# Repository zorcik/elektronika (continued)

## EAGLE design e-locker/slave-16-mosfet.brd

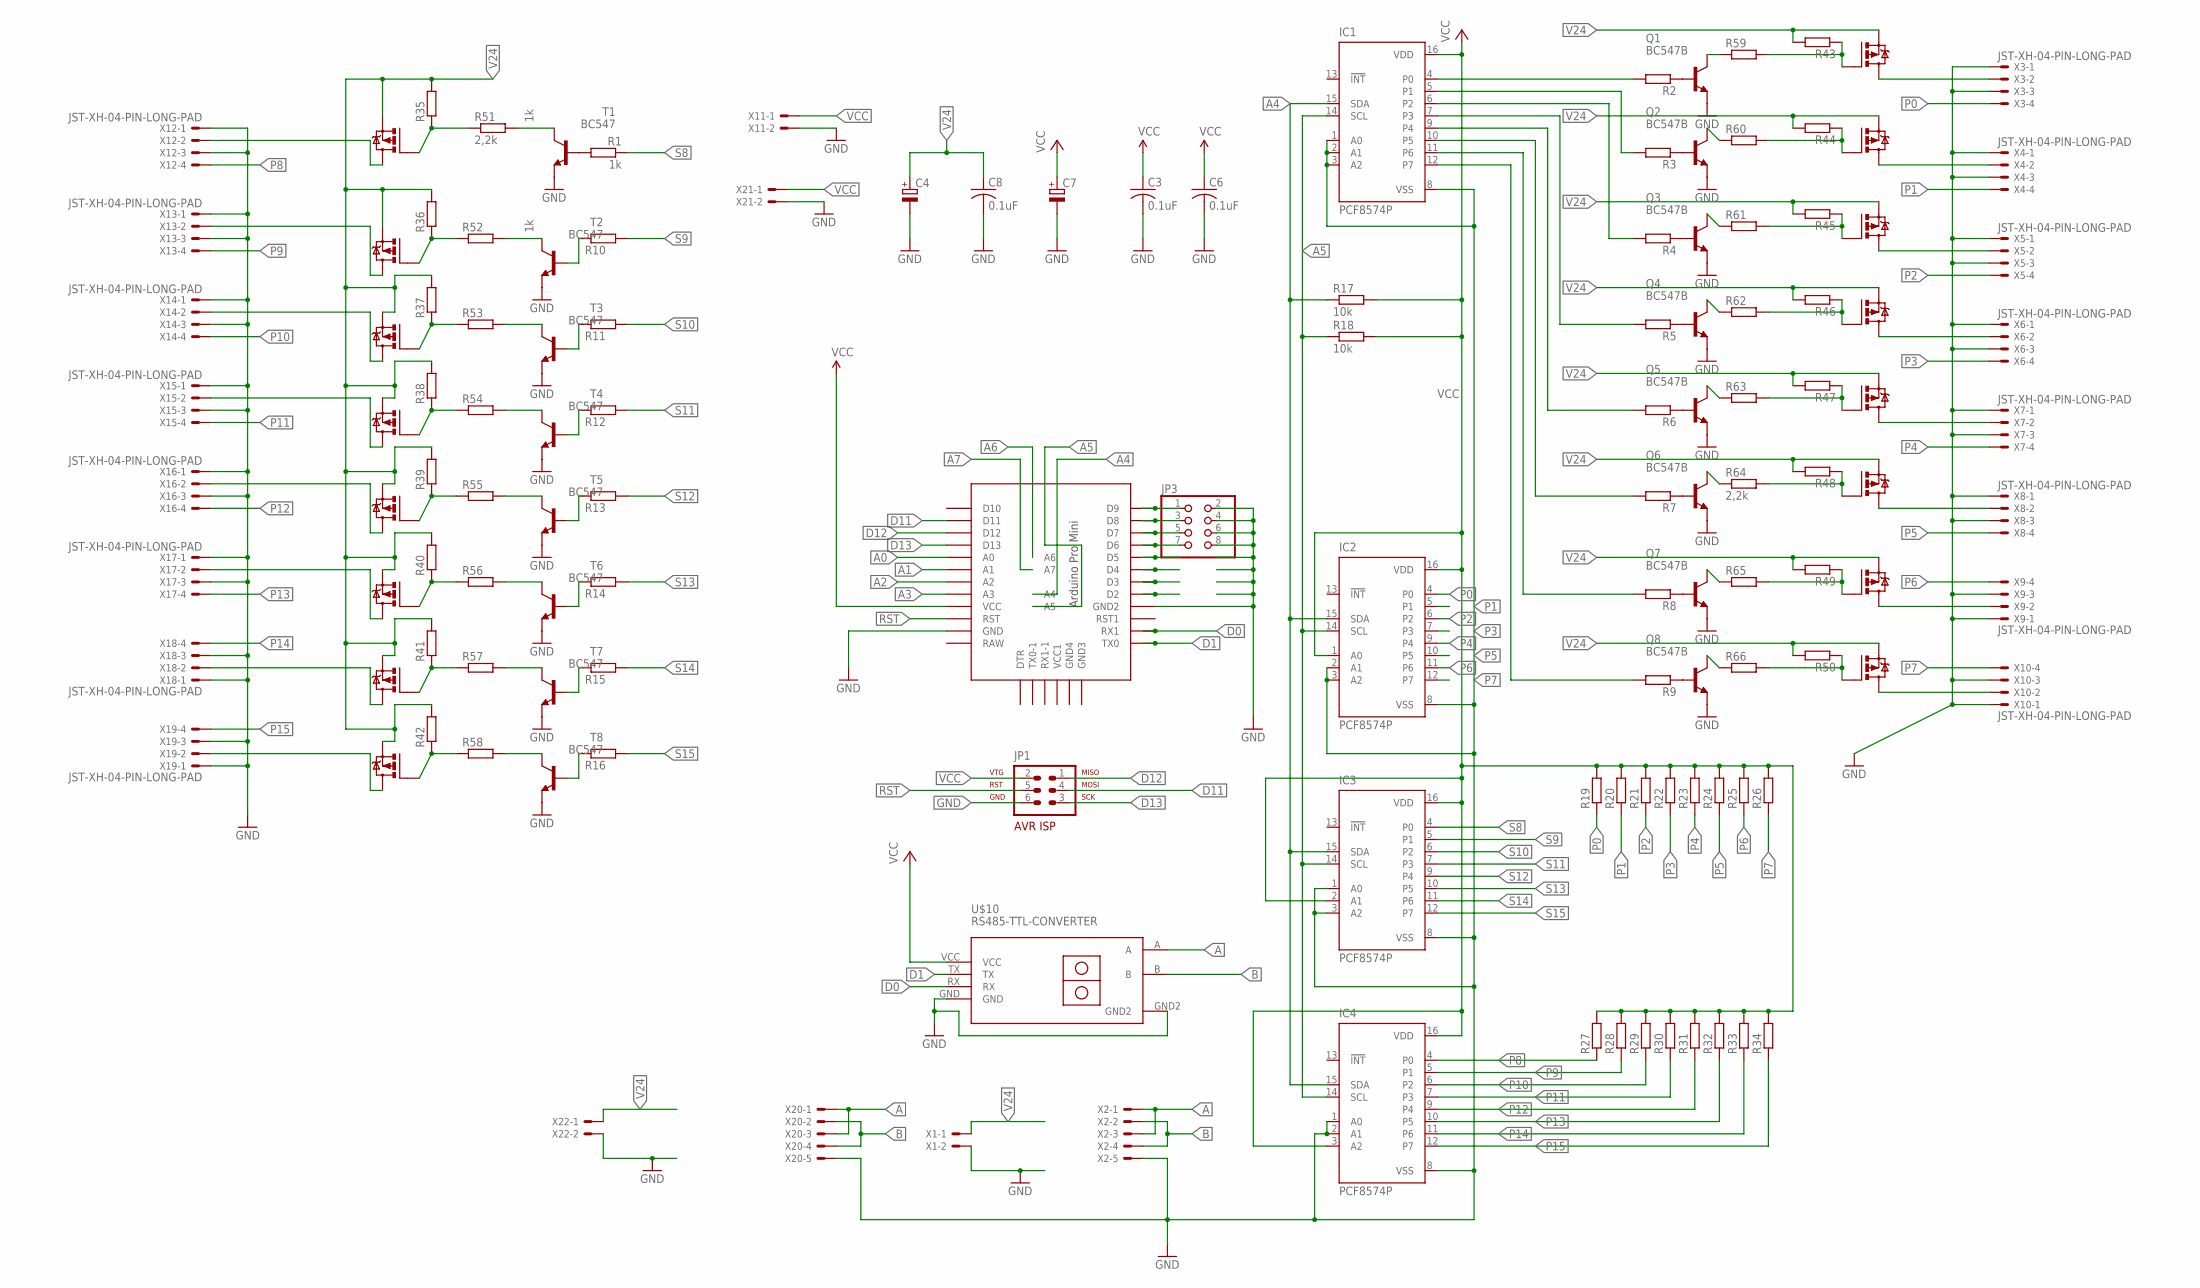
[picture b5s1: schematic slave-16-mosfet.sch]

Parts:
C3, C6, C8: 0.1uF; C0805
C4, C7: CPOL-EUSANYO_SMD_C6; SANYO-OSCON_SMD_C6
IC1, IC2, IC3, IC4: PCF8574P; DIL16
JP1: AVR-ISP-6
JP3: PINHD-2X4; 2X04
Q1, Q2, Q3, Q4, Q5, Q6, Q7, Q8: BC547B; TO92
R1, R35, R36: 1k; R1206
R2, R3, R4, R5, R6, R7, R8, R9, R10, R11, R12, R13, R14, R15, R16, R19, R20, R21, R22, R23, R24, R25, R26, R27, R28, R29, R30, R31, R32, R33, R34, R37, R38, R39, R40, R41, R42, R43, R44, R45, R46, R47, R48, R49, R50, R52, R53, R54, R55, R56, R57, R58, R59, R60, R61, R62, R63, R65, R66: RR1206; R1206
R17, R18: 10k; R1206
R51, R64: 2,2k; R1206
T1, T2, T3, T4, T5, T6, T7, T8: BC547; TO92
U$1, U$2, U$3, U$4, U$5, U$6, U$7, U$8, U$12, U$13, U$14, U$15, U$16, U$17, U$18, U$19: IRF9530; TO220BV
U$10: RS485-TTL-CONVERTER
U$20: PRO-MINI-2
X1, X11, X21, X22: JST-XH-02-PIN-LONG-PAD; JST-XH-02-PACKAGE-LONG-PAD
X2, X20: JST-XH-05-PIN-LONG-PAD; JST-XH-05-PACKAGE-LONG-PAD
X3, X4, X5, X6, X7, X8, X9, X10, X12, X13, X14, X15, X16, X17, X18, X19: JST-XH-04-PIN-LONG-PAD; JST-XH-04-PACKAGE-LONG-PAD

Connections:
A: U$10.A, X2.1, X2.3, X20.1, X20.3
A0: U$20.A0
A1: U$20.A1
A2: U$20.A2
A3: U$20.A3
A4: IC1.15 (SDA), IC2.15 (SDA), IC3.15 (SDA), IC4.15 (SDA), R17.1, U$20.A4
A5: IC1.14 (SCL), IC2.14 (SCL), IC3.14 (SCL), IC4.14 (SCL), R18.1, U$20.A5
A6: U$20.A6
A7: U$20.A7
B: U$10.B, X2.2, X2.4, X20.2, X20.4
D0: U$10.RX, U$20.RX1
D1: U$10.TX, U$20.TX0
D11: JP1.4, U$20.D11
D12: JP1.1, U$20.D12
D13: JP1.3, U$20.D13
GND: C3.2, C4.-, C6.2, C7.-, C8.2, IC1.1 (A0), IC1.2 (A1), IC1.3 (A2), IC1.8 (VSS), IC2.2 (A1), IC2.3 (A2), IC2.8 (VSS), IC3.1 (A0), IC3.3 (A2), IC3.8 (VSS), IC4.1 (A0), IC4.2 (A1), IC4.8 (VSS), JP1.6, JP3.2, JP3.4, JP3.6, JP3.8, Q1.1 (E), Q2.1 (E), Q3.1 (E), Q4.1 (E), Q5.1 (E), Q6.1 (E), Q7.1 (E), Q8.1 (E), T1.1 (E), T2.1 (E), T3.1 (E), T4.1 (E), T5.1 (E), T6.1 (E), T7.1 (E), T8.1 (E), U$10.GND, U$10.GND2, U$20.GND, U$20.GND1 (GND2), X1.2, X2.5, X3.1, X3.3, X4.1, X4.3, X5.1, X5.3, X6.1, X6.3, X7.1, X7.3, X8.1, X8.3, X9.1, X9.3, X10.1, X10.3, X11.2, X12.1, X12.3, X13.1, X13.3, X14.1, X14.3, X15.1, X15.3, X16.1, X16.3, X17.1, X17.3, X18.1, X18.3, X19.1, X19.3, X20.5, X21.2, X22.2
unnamed: Q8.2 (B), R9.1
unnamed: Q7.2 (B), R8.1
unnamed: R15.1, T7.2 (B)
unnamed: Q6.2 (B), R7.1
unnamed: Q5.2 (B), R6.1
unnamed: Q4.2 (B), R5.1
unnamed: Q3.2 (B), R4.1
unnamed: Q2.2 (B), R3.1
unnamed: Q1.2 (B), R2.1
unnamed: R44.1, R60.2, U$2.G
unnamed: R45.1, R61.2, U$3.G
unnamed: R46.1, R62.2, U$4.G
unnamed: U$1.D, X3.2
unnamed: U$2.D, X4.2
unnamed: U$3.D, X5.2
unnamed: U$4.D, X6.2
unnamed: JP3.7, U$20.D6
unnamed: JP3.5, U$20.D7
unnamed: JP3.3, U$20.D8
unnamed: JP3.1, U$20.D9
unnamed: R1.2, T1.2 (B)
unnamed: R35.1, R51.1, U$12.G
unnamed: R42.1, R58.1, U$19.G
unnamed: R40.1, R56.1, U$17.G
unnamed: IC1.4 (P0), R2.2
unnamed: IC1.5 (P1), R3.2
unnamed: IC1.6 (P2), R4.2
unnamed: IC1.7 (P3), R5.2
unnamed: IC1.9 (P4), R6.2
unnamed: IC1.10 (P5), R7.2
unnamed: IC1.11 (P6), R8.2
unnamed: IC1.12 (P7), R9.2
unnamed: R16.1, T8.2 (B)
unnamed: R14.1, T6.2 (B)
unnamed: U$5.D, X7.2
unnamed: U$6.D, X8.2
unnamed: U$7.D, X9.2
unnamed: R39.1, R55.1, U$16.G
unnamed: R41.1, R57.1, U$18.G
unnamed: R13.1, T5.2 (B)
unnamed: U$12.D, X12.2
unnamed: U$13.D, X13.2
unnamed: U$14.D, X14.2
unnamed: U$15.D, X15.2
unnamed: U$16.D, X16.2
unnamed: U$17.D, X17.2
unnamed: U$18.D, X18.2
unnamed: U$19.D, X19.2
unnamed: U$8.D, X10.2
unnamed: R38.1, R54.1, U$15.G
unnamed: R50.1, R66.2, U$8.G
unnamed: R12.1, T4.2 (B)
unnamed: R37.1, R53.1, U$14.G
unnamed: R49.1, R65.2, U$7.G
unnamed: R11.1, T3.2 (B)
unnamed: R10.1, T2.2 (B)
unnamed: R36.1, R52.1, U$13.G
unnamed: R48.1, R64.2, U$6.G
unnamed: R47.1, R63.2, U$5.G
unnamed: R58.2, T8.3 (C)
unnamed: R57.2, T7.3 (C)
unnamed: R56.2, T6.3 (C)
unnamed: R55.2, T5.3 (C)
unnamed: R54.2, T4.3 (C)
unnamed: R53.2, T3.3 (C)
unnamed: R52.2, T2.3 (C)
unnamed: R51.2, T1.3 (C)
unnamed: Q8.3 (C), R66.1
unnamed: Q7.3 (C), R65.1
unnamed: Q6.3 (C), R64.1
unnamed: Q5.3 (C), R63.1
unnamed: Q4.3 (C), R62.1
unnamed: Q3.3 (C), R61.1
unnamed: Q2.3 (C), R60.1
unnamed: Q1.3 (C), R59.1
unnamed: R43.1, R59.2, U$1.G
P0: IC2.4 (P0), R19.1, X3.4
P1: IC2.5 (P1), R20.1, X4.4
P2: IC2.6 (P2), R21.1, X5.4
P3: IC2.7 (P3), R22.1, X6.4
P4: IC2.9 (P4), R23.1, X7.4
P5: IC2.10 (P5), R24.1, X8.4
P6: IC2.11 (P6), R25.1, X9.4
P7: IC2.12 (P7), R26.1, X10.4
P8: IC4.4 (P0), R27.1, X12.4
P9: IC4.5 (P1), R28.1, X13.4
P10: IC4.6 (P2), R29.1, X14.4
P11: IC4.7 (P3), R30.1, X15.4
P12: IC4.9 (P4), R31.1, X16.4
P13: IC4.10 (P5), R32.1, X17.4
P14: IC4.11 (P6), R33.1, X18.4
P15: IC4.12 (P7), R34.1, X19.4
RST: JP1.5, U$20.RST
S8: IC3.4 (P0), R1.1
S9: IC3.5 (P1), R10.2
S10: IC3.6 (P2), R11.2
S11: IC3.7 (P3), R12.2
S12: IC3.9 (P4), R13.2
S13: IC3.10 (P5), R14.2
S14: IC3.11 (P6), R15.2
S15: IC3.12 (P7), R16.2
V24: C4.+, C8.1, R35.2, R36.2, R37.2, R38.2, R39.2, R40.2, R41.2, R42.2, R43.2, R44.2, R45.2, R46.2, R47.2, R48.2, R49.2, R50.2, U$1.S, U$2.S, U$3.S, U$4.S, U$5.S, U$6.S, U$7.S, U$8.S, U$12.S, U$13.S, U$14.S, U$15.S, U$16.S, U$17.S, U$18.S, U$19.S, X1.1, X22.1
VCC: C3.1, C6.1, C7.+, IC1.16 (VDD), IC2.1 (A0), IC2.16 (VDD), IC3.2 (A1), IC3.16 (VDD), IC4.3 (A2), IC4.16 (VDD), JP1.2, R17.2, R18.2, R19.2, R20.2, R21.2, R22.2, R23.2, R24.2, R25.2, R26.2, R27.2, R28.2, R29.2, R30.2, R31.2, R32.2, R33.2, R34.2, U$10.VCC, U$20.VCC, X11.1, X21.1

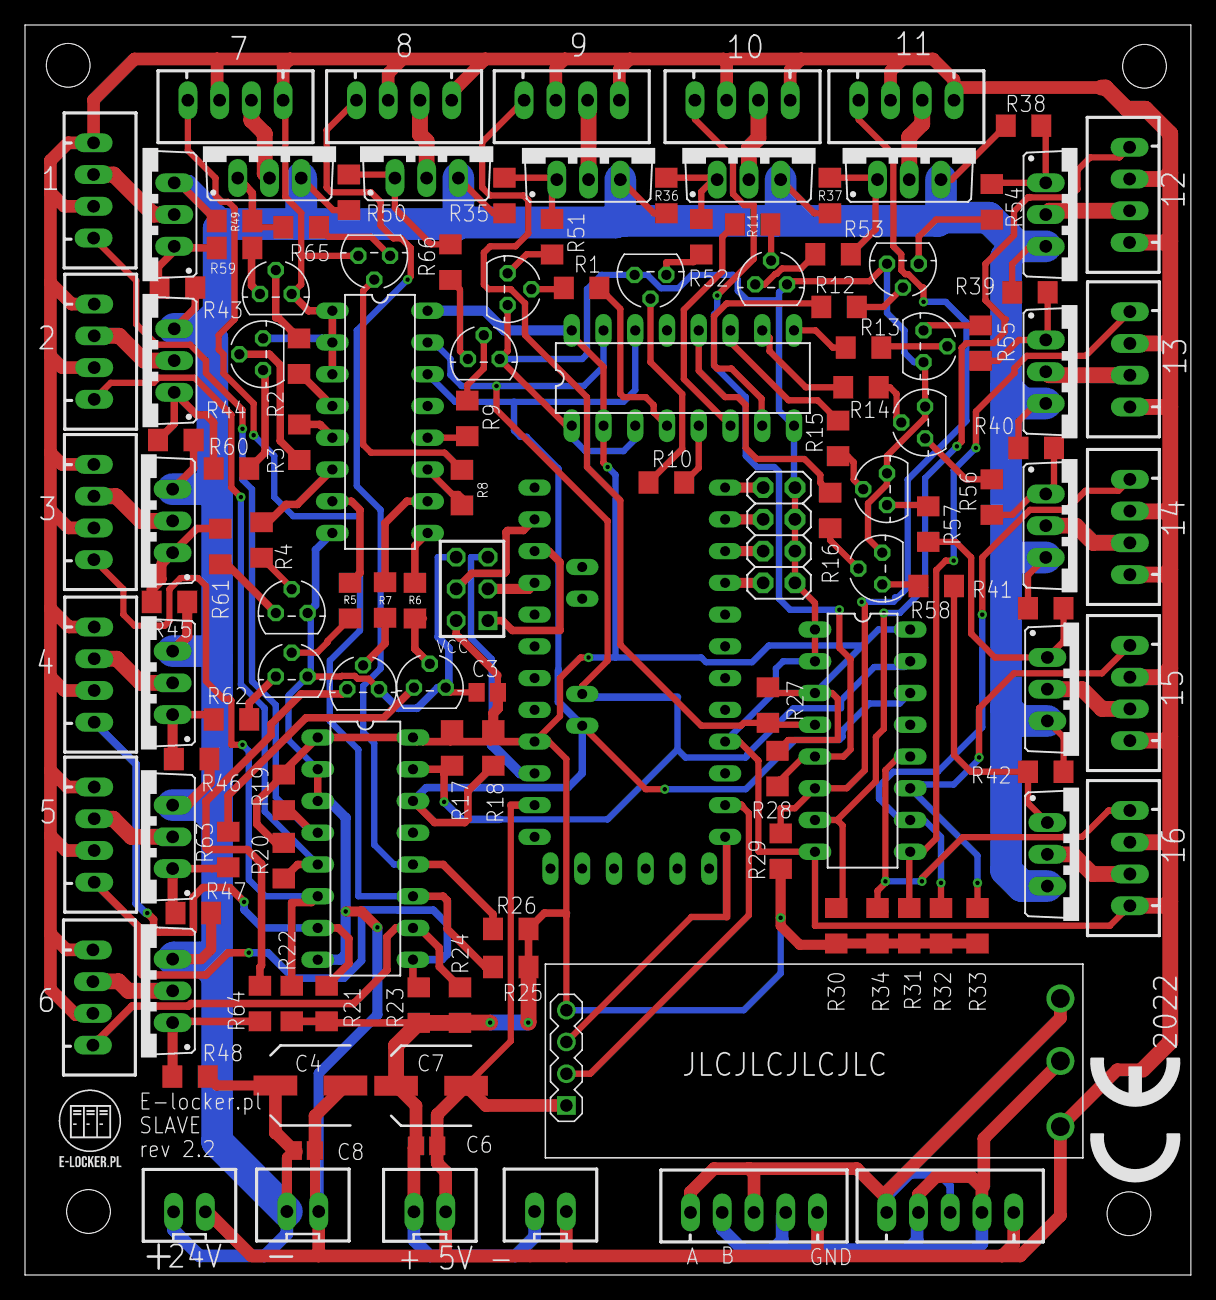
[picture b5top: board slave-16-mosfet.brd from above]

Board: 2 copper layers, 93.3 x 100.0 mm, 135 parts (0 on the bottom side), 113 nets.

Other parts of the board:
U$9: ELOCKER
U$11: CE_7.3MM

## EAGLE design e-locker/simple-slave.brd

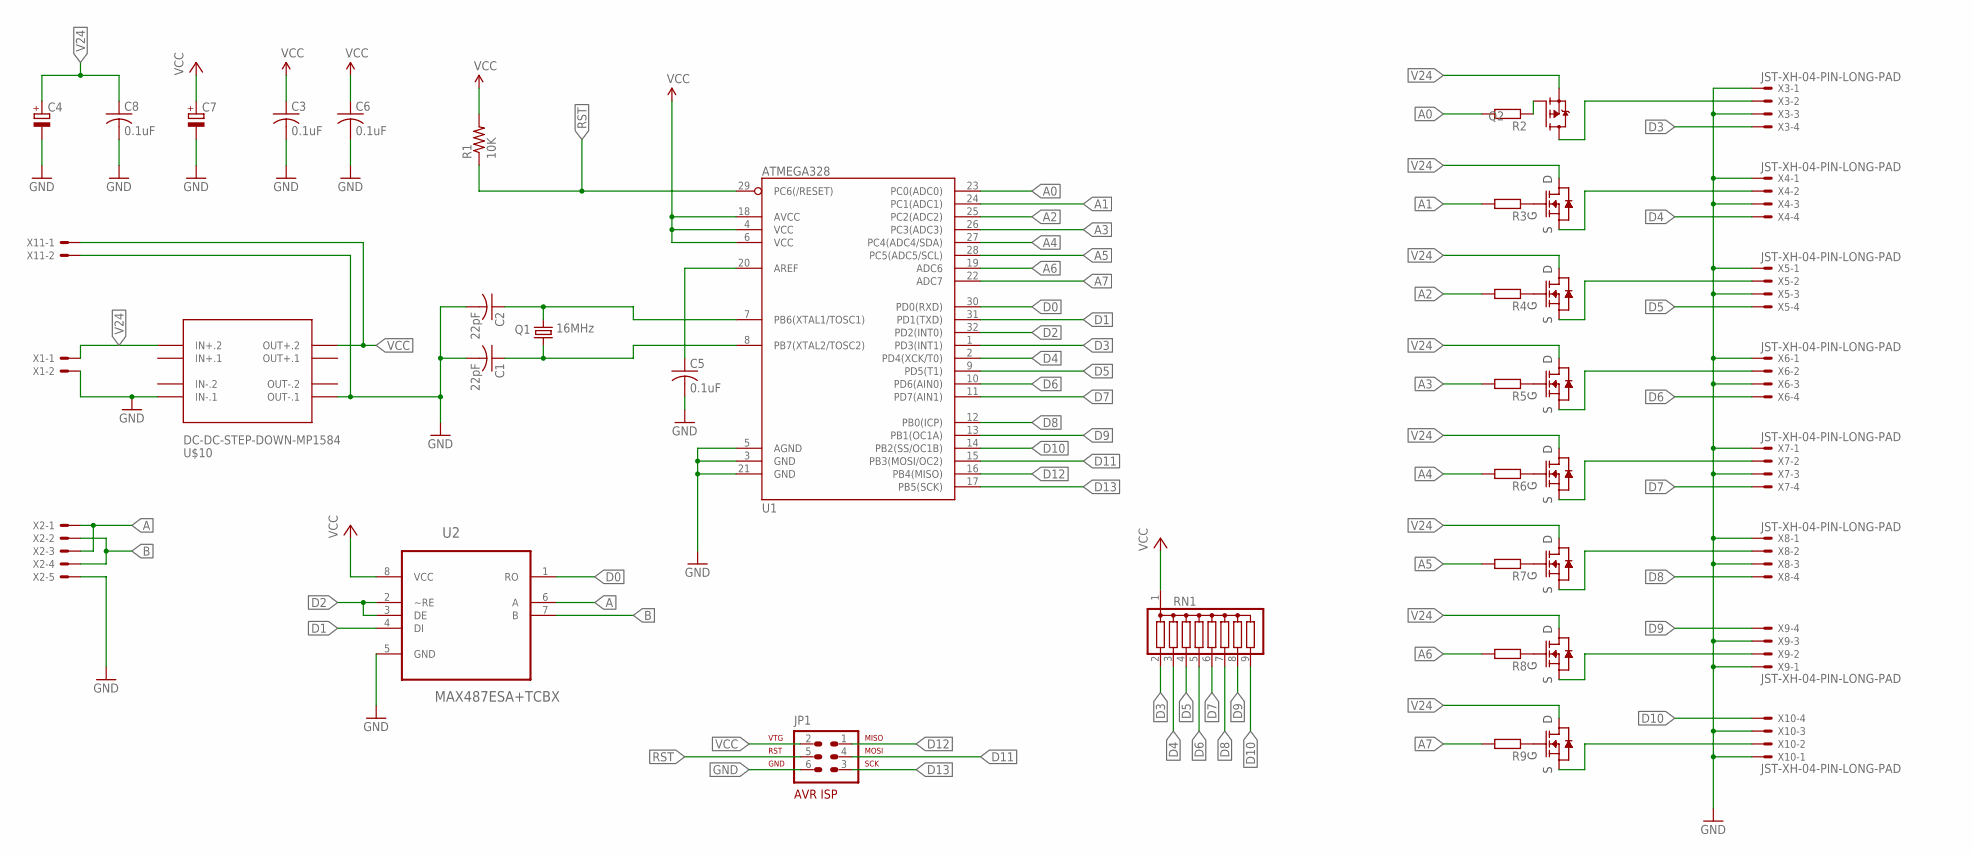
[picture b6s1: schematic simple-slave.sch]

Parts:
C1, C2: 22pF; C1206
C3, C5, C6, C8: 0.1uF; C0805
C4, C7: CPOL-EUSANYO_SMD_C6; SANYO-OSCON_SMD_C6
JP1: AVR-ISP-6
Q1: 16MHz; HC49/S
Q2: SPD30P06PTO252; TO252
R1: 10K; R1206
R2, R3, R4, R5, R6, R7, R8, R9: RR1206; R1206
RN1: G08R; SIL9
U1: ATMEGA328; TQFP32-08
U2: MAX487ESA+TCBX; SOIC127P600X175-8N
U$2, U$3, U$4, U$5, U$6, U$7, U$8: MOSFET-NTO252; TO252
U$10: DC-DC-STEP-DOWN-MP1584
X1, X11: JST-XH-02-PIN-LONG-PAD; JST-XH-02-PACKAGE-LONG-PAD
X2: JST-XH-05-PIN-LONG-PAD; JST-XH-05-PACKAGE-LONG-PAD
X3, X4, X5, X6, X7, X8, X9, X10: JST-XH-04-PIN-LONG-PAD; JST-XH-04-PACKAGE-LONG-PAD

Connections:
A: U2.6 (A), X2.1, X2.3
A0: R2.2, U1.23 (PC0(ADC0))
A1: R3.2, U1.24 (PC1(ADC1))
A2: R4.2, U1.25 (PC2(ADC2))
A3: R5.2, U1.26 (PC3(ADC3))
A4: R6.2, U1.27 (PC4(ADC4/SDA))
A5: R7.2, U1.28 (PC5(ADC5/SCL))
A6: R8.2, U1.19 (ADC6)
A7: R9.2, U1.22 (ADC7)
AREF: C5.1, U1.20 (AREF)
B: U2.7 (B), X2.2, X2.4
D0: U1.30 (PD0(RXD)), U2.1 (RO)
D1: U1.31 (PD1(TXD)), U2.4 (DI)
D2: U1.32 (PD2(INT0)), U2.2 (~RE), U2.3 (DE)
D3: RN1.2, U1.1 (PD3(INT1)), X3.4
D4: RN1.3, U1.2 (PD4(XCK/T0)), X4.4
D5: RN1.4, U1.9 (PD5(T1)), X5.4
D6: RN1.5, U1.10 (PD6(AIN0)), X6.4
D7: RN1.6, U1.11 (PD7(AIN1)), X7.4
D8: RN1.7, U1.12 (PB0(ICP)), X8.4
D9: RN1.8, U1.13 (PB1(OC1A)), X9.4
D10: RN1.9, U1.14 (PB2(SS/OC1B)), X10.4
D11: JP1.4, U1.15 (PB3(MOSI/OC2))
D12: JP1.1, U1.16 (PB4(MISO))
D13: JP1.3, U1.17 (PB5(SCK))
GND: C1.2, C2.2, C3.2, C4.-, C5.2, C6.2, C7.-, C8.2, JP1.6, U1.3 (GND), U1.5 (AGND), U1.21 (GND), U2.5 (GND), U$10.IN-.1, U$10.OUT-.1, X1.2, X2.5, X3.1, X3.3, X4.1, X4.3, X5.1, X5.3, X6.1, X6.3, X7.1, X7.3, X8.1, X8.3, X9.1, X9.3, X10.1, X10.3, X11.2
unnamed: Q2.1 (G), R2.1
unnamed: R3.1, U$2.P1 (G)
unnamed: R4.1, U$3.P1 (G)
unnamed: R5.1, U$4.P1 (G)
unnamed: R6.1, U$5.P1 (G)
unnamed: R7.1, U$6.P1 (G)
unnamed: R8.1, U$7.P1 (G)
unnamed: R9.1, U$8.P1 (G)
unnamed: Q2.3 (D), X3.2
unnamed: U$2.P3 (S), X4.2
unnamed: U$3.P3 (S), X5.2
unnamed: U$4.P3 (S), X6.2
unnamed: U$5.P3 (S), X7.2
unnamed: U$6.P3 (S), X8.2
unnamed: U$7.P3 (S), X9.2
unnamed: U$8.P3 (S), X10.2
unnamed: C2.1, Q1.2, U1.7 (PB6(XTAL1/TOSC1))
unnamed: C1.1, Q1.1, U1.8 (PB7(XTAL2/TOSC2))
RST: JP1.5, R1.1, U1.29 (PC6(/RESET))
V24: C4.+, C8.1, Q2.2 (S), U$2.P2 (D), U$3.P2 (D), U$4.P2 (D), U$5.P2 (D), U$6.P2 (D), U$7.P2 (D), U$8.P2 (D), U$10.IN+.2, X1.1
VCC: C3.1, C6.1, C7.+, JP1.2, R1.2, RN1.1, U1.4 (VCC), U1.6 (VCC), U1.18 (AVCC), U2.8 (VCC), U$10.OUT+.2, X11.1

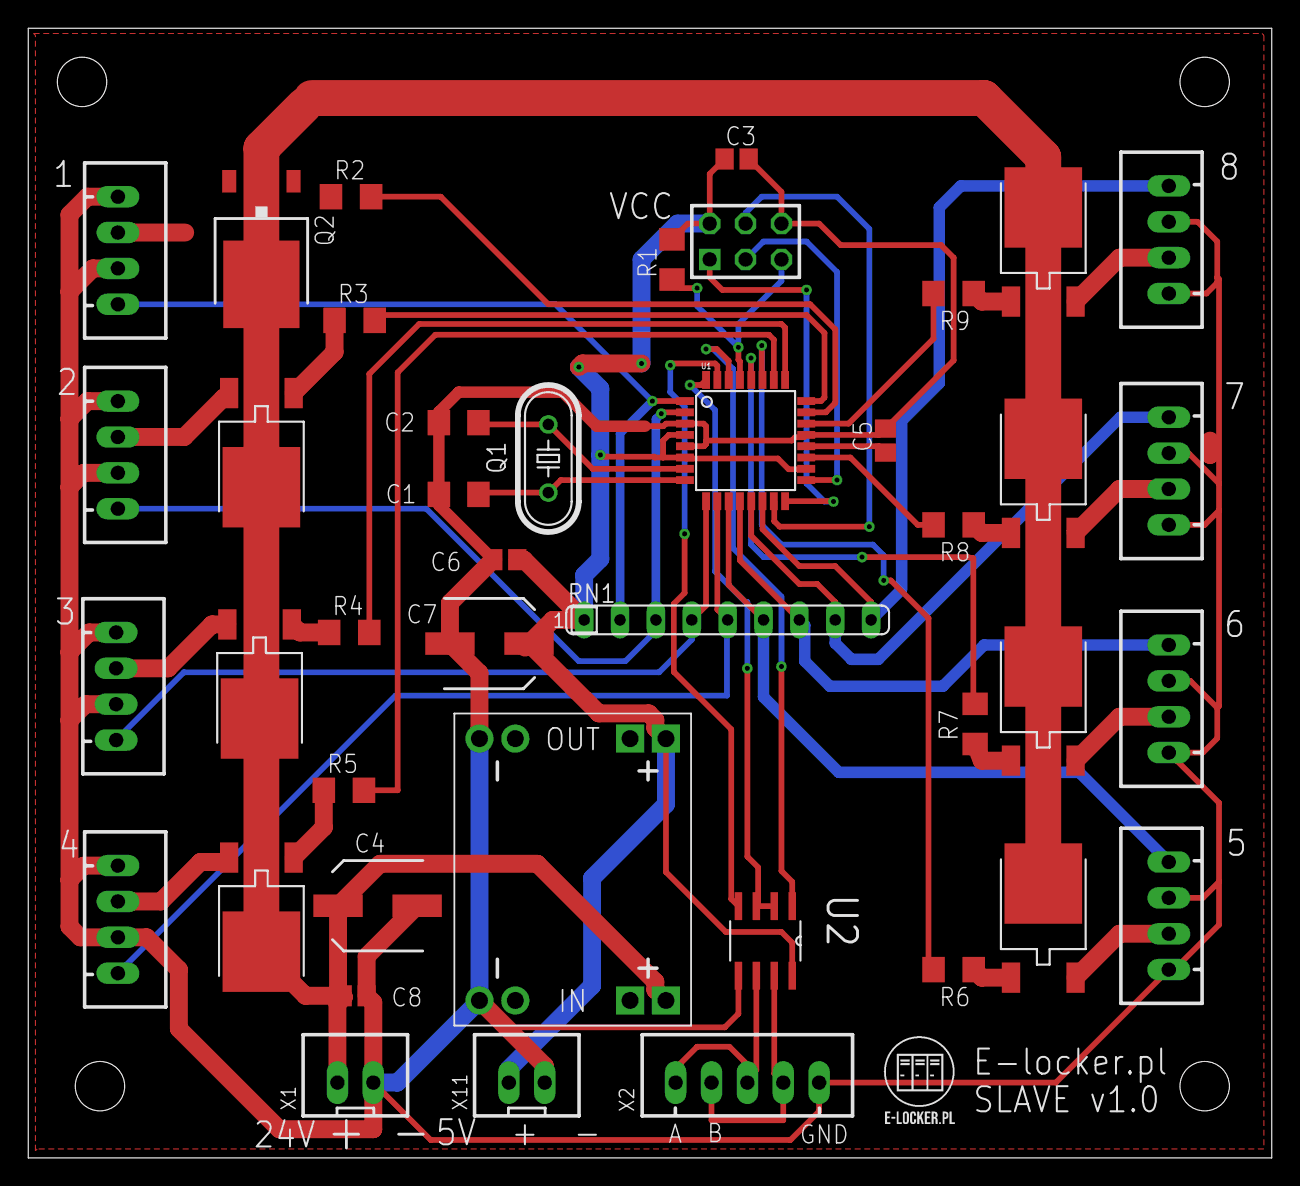
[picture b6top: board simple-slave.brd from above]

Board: 2 copper layers, 88.1 x 80.0 mm, 43 parts (0 on the bottom side), 47 nets.

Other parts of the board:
U$9: ELOCKER

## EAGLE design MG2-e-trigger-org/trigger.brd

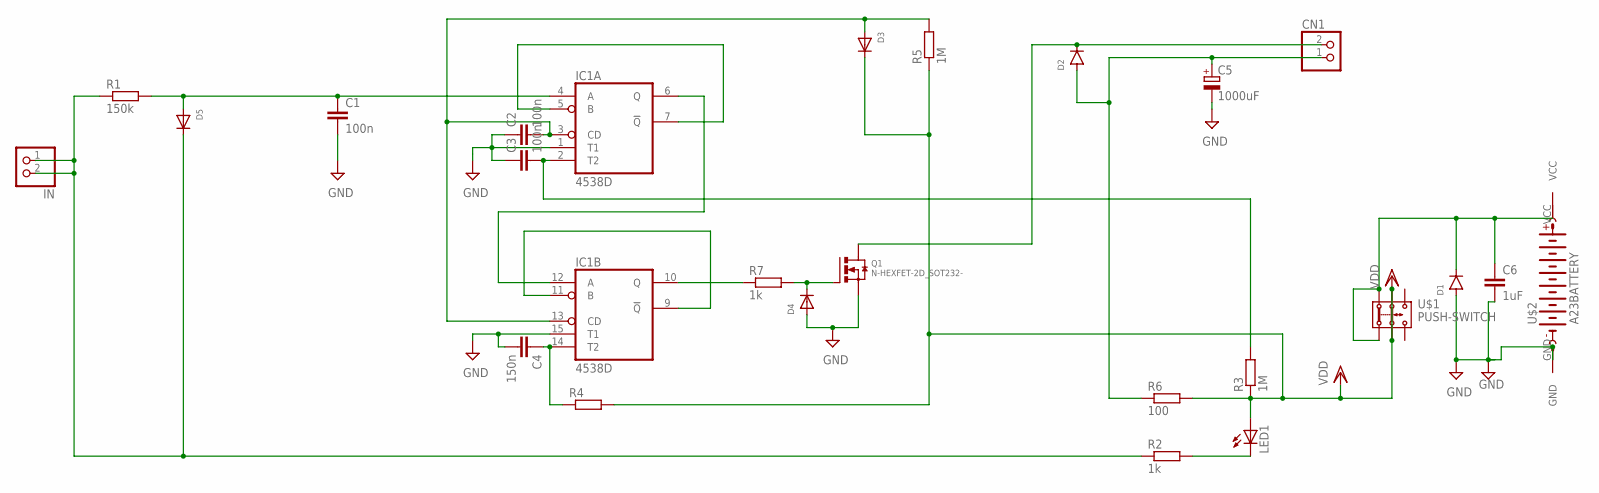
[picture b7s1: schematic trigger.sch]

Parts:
C1, C2, C3: 100n; C0805
C4: 150n; C0805
C5: 1000uF; E5-6
C6: 1uF; C1808
CN1: JST_2PIN-THM; JST-PH-2-THM
D1, D2: D-SMB; SMB
D3, D4, D5: DIODESOD-123; SOD-123
IC1: 4538D; SO16
IN: JST_2PIN-THM; JST-PH-2-THM
LED1: LED3MM
Q1: N-HEXFET-2D_SOT232-; SOT223
R1: 150k; R1206
R2, R7: 1k; R1206
R3, R5: 1M; R1206
R4: RR1206; R1206
R6: 100; R2512
U$1: PUSH-SWITCH
U$2: A23BATTERY; A23

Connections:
GND: C1.2, C2.1, C3.1, C4.2, C5.-, C6.2, D1.2 (A), D4.A, IC1.1 (T1), IC1.8 (VSS), IC1.15 (T1), Q1.3 (S), U$2.GND
unnamed: C6.1, D1.1 (C), U$1.P$1 (1.2), U$1.P$5 (1.1), U$2.VCC
unnamed: IC1.9 (!Q), IC1.11 (B)
unnamed: IC1.5 (B), IC1.7 (!Q)
unnamed: IC1.6 (Q), IC1.12 (A)
unnamed: D5.C, IN.1 (2), IN.2 (1), R1.1, R2.1
unnamed: C1.1, D5.A, IC1.4 (A), R1.2
unnamed: LED1.K (C), R2.2
unnamed: C4.1, IC1.14 (T2), R4.1
unnamed: C3.2, IC1.2 (T2), R3.2
unnamed: C2.2, D3.A, IC1.3 (CD), IC1.13 (CD), R5.2
unnamed: IC1.10 (Q), R7.1
unnamed: D4.C, Q1.1 (G), R7.2
unnamed: CN1.2 (1), D2.1 (C), Q1.2 (D), Q1.4 (D)
unnamed: C5.+, CN1.1 (2), D2.2 (A), R6.1
VDD: D3.C, IC1.16 (VDD), LED1.A, R3.1, R4.2, R5.1, R6.2, U$1.P$2 (2.2), U$1.P$6 (2.1)

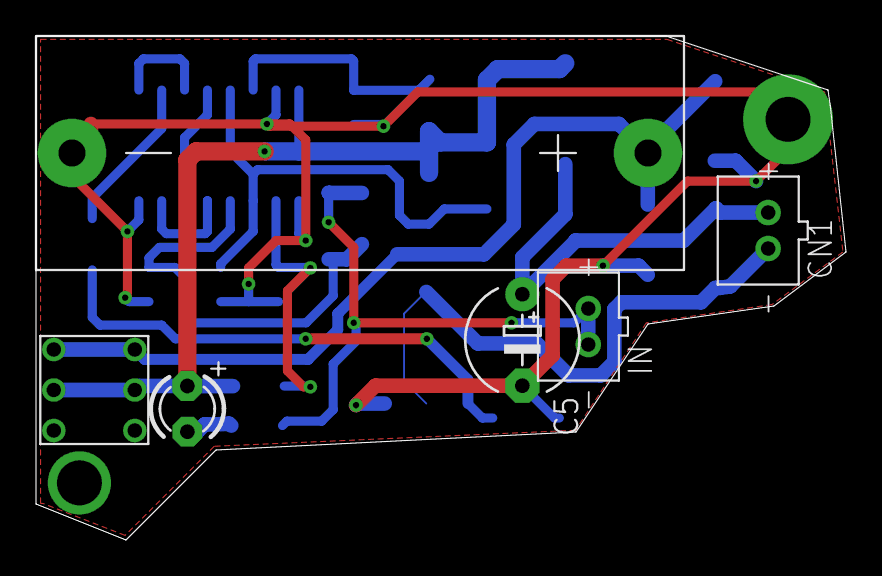
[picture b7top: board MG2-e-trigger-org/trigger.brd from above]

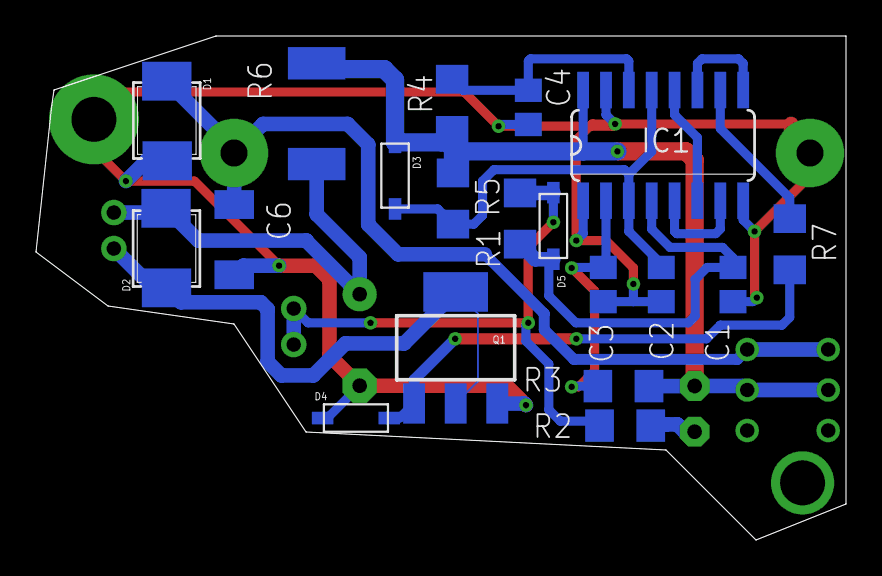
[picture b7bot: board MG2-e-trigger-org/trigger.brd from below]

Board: 2 copper layers, 45.0 x 28.0 mm, 25 parts (19 on the bottom side), 16 nets.

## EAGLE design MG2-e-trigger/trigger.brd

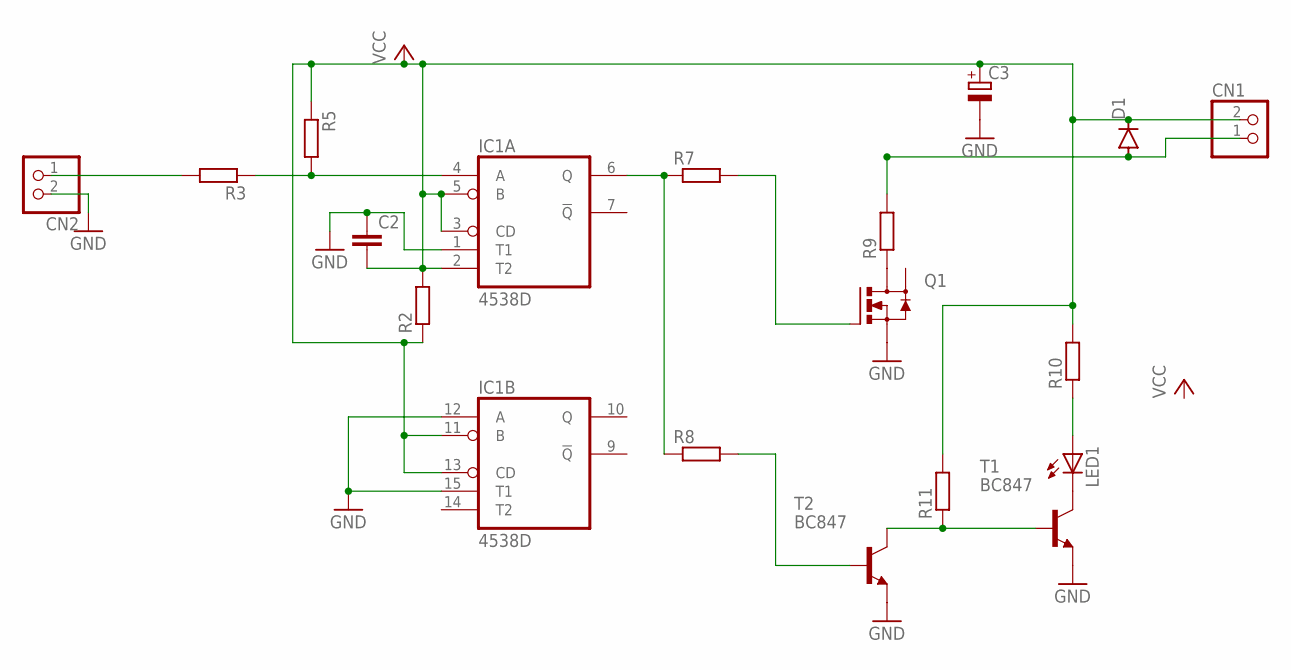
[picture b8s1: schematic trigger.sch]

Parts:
C2: C; C0805
C3: CPOL-EUE5-13; E5-13
CN1, CN2: JST_2PIN-THM; JST-PH-2-THM
D1: DIODE-DO214AC; DO214AC
IC1: 4538D; SO16
LED1: LED3MM
Q1: MOSFET_N_SOT223; SOT223
R2, R3, R5, R7, R8, R9: RR1206; R1206
R10, R11: R; R0805
T1, T2: BC847; SOT23

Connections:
GND: C2.1, C3.-, CN2.2 (1), IC1.1 (T1), IC1.12 (A), IC1.15 (T1), Q1.3 (S), T1.2 (E), T2.2 (E); also elsewhere on the board
unnamed: LED1.K (C), T1.3 (C)
unnamed: CN2.1 (2), R3.2
unnamed: IC1.4 (A), R3.1, R5.2
unnamed: IC1.6 (Q), R7.1, R8.1
unnamed: Q1.2 (D), R9.1
unnamed: R8.2, T2.1 (B)
unnamed: CN1.1 (2), D1.A, R9.2
unnamed: R11.1, T1.1 (B), T2.3 (C)
unnamed: LED1.A, R10.1
unnamed: Q1.1 (G), R7.2
VCC: C2.2, C3.+, CN1.2 (1), D1.C, IC1.2 (T2), IC1.3 (CD), IC1.5 (B), IC1.11 (B), IC1.13 (CD), R2.1, R2.2, R5.1, R10.2, R11.2; also elsewhere on the board
VDD: IC1.16 (VDD)
VSS: IC1.8 (VSS)

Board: 2 copper layers, 20 parts (0 on the bottom side), 13 nets, no tracks yet.

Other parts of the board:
C1: E5-6
U$1: A23BATTERY; A23
U$3: PUSH-SWITCH

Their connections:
GND: C1.-, U$1.GND; also elsewhere on the board
unnamed: U$1.VCC, U$3.P$3, U$3.P$4
VCC: C1.+, U$3.P$2, U$3.P$6; also elsewhere on the board

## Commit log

2020-11-12 Libs and universal sensor WIP
2020-11-13 Old projects
2020-11-13 MCU changes
2020-11-17 Temp sensor
2020-11-17 current sensor
2020-11-19 light switch
2021-01-20 temp sensor changes
2021-01-21 new files
2021-01-23 Roller shutter
2021-01-26 Roller shutter ark change
2021-02-07 Roller shutter, heat controller WIP and a new light switch input board
2021-02-08 Temp sensor, NTC
2021-02-11 Heat controller schematic
2021-02-17 Heat controller as MCU mod
2021-02-17 MLU board
2021-02-25 RF LED
2021-02-26 adds capacitor to each WS2812 LED
2021-02-27 adds SSR to roller shutter controller
2021-03-01 MG2 trigger
2021-03-10 trigger change
2021-09-07 e-locker simple slave board WIP
2021-09-07 simple slave
2021-09-07 RPi board
2021-09-09 Rpi master board
2021-09-27 elocker-slave16
2021-09-28 arduino footprint change
2021-09-29 incorrect mosfets - WIP
2021-10-04 slave p-channel mosfet
2021-10-08 new master controller based on ESP32 and SIM800L
2021-10-11 text changes
2021-10-13 slave 16
2021-10-13 elocker slave rev 2.0 final
2021-11-10 3d master
2021-11-10 master new revision
2021-11-10 sim800l v2 schematics
2021-11-15 IRF version
2021-11-30 new master and slave16 changes
2021-12-16 ESP32 footprint change
2021-12-28 mosfet slave fix
2021-12-29 fixes
2022-01-23 New 8 port light switch controller
2022-01-23 board
2022-01-25 minor movement
2022-01-25 temp meter
2022-03-01 roller shutter rs485
2022-05-10 QR code reader header
2022-11-17 v1.7
2023-02-17 temp meter - one sensor
2023-02-19 ds one sensor
